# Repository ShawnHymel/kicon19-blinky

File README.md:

Blinky Pin for KiCon 2019
=========================

Pin badge developed for KiCon 2019. Workshop used to teach people the basics of KiCad.

Getting Started
---------------

Follow the instructions found in the [Worksheet - Intro to KiCad PDF](https://github.com/ShawnHymel/kicon19-blinky/blob/master/Documentation/Worksheet%20-%20Intro%20to%20KiCad.pdf).

Bill of Materials (BOM)
-----------------------

To build the pin/badge, refer to the [BOM file found here](https://github.com/ShawnHymel/kicon19-blinky/blob/master/Hardware/kicon19-blinky-bom.csv).

License
-------

The code is beerware; if you see me at the local, and you've found the code helpful, please buy me a round!

Board schematic and layout design found in the [Hardware directory](https://github.com/ShawnHymel/kicon19-blinky/tree/master/Hardware) are [CC BY 4.0](https://creativecommons.org/licenses/by/4.0/).

[Worksheet](https://github.com/ShawnHymel/kicon19-blinky/blob/master/Documentation/Worksheet%20-%20Intro%20to%20KiCad.pdf) is [CC BY 4.0](https://creativecommons.org/licenses/by/4.0/).

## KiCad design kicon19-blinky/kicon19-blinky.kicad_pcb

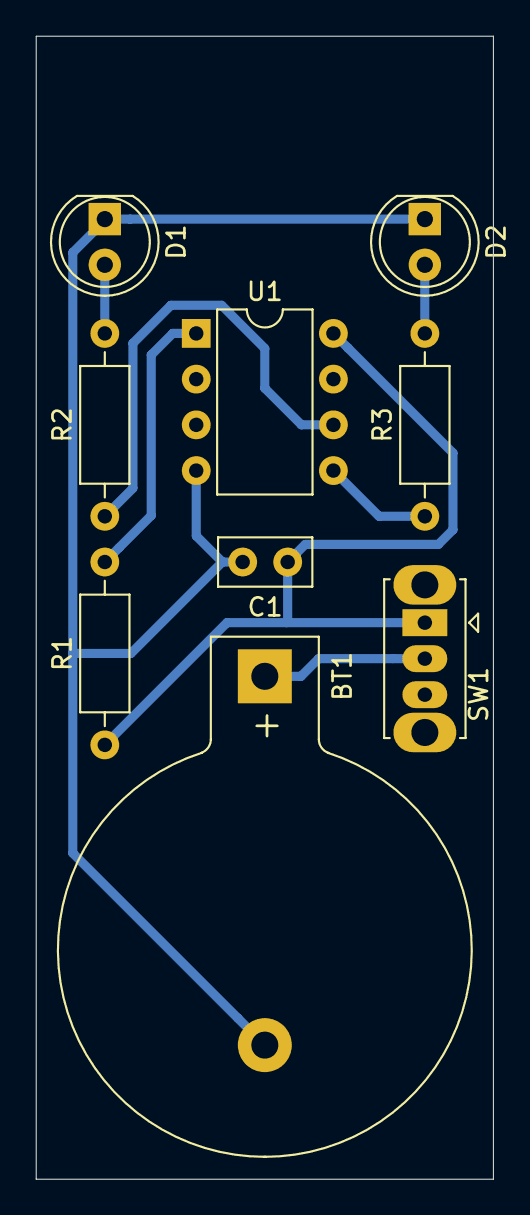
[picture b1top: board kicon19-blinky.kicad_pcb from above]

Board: 2 copper layers, 25.4 x 63.5 mm, 9 parts (0 on the bottom side), 8 nets.

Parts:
BT1: Battery_Cell; BatteryHolder_Keystone_103_1x20mm
C1: 10uF; C_Disc_D5.0mm_W2.5mm_P2.50mm
D1, D2: LED; LED_D5.0mm
R1: 10k; R_Axial_DIN0207_L6.3mm_D2.5mm_P10.16mm_Horizontal
R2, R3: 100; R_Axial_DIN0207_L6.3mm_D2.5mm_P10.16mm_Horizontal
SW1: SW_SPDT; SW_Slide_1P2T_CK_OS102011MS2Q
U1: ATtiny85-20PU; DIP-8_W7.62mm

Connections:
unnamed: BT1.1, SW1.2
unnamed: BT1.2, C1.2, D1.1, D2.1, U1.4
unnamed: C1.1, R1.1, SW1.1, U1.8
unnamed: D1.2, R2.2
unnamed: D2.2, R3.2
unnamed: R1.2, U1.1
unnamed: R2.1, U1.6
unnamed: R3.1, U1.5

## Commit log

2019-04-05 Initial schematic and part placement
2019-04-07 Finished board, added Arduino program
2019-04-07 Updated Arduino code for more linear blink
2019-04-22 Reorganized folders
2019-04-25 Updated sketch for low power. Added worksheet.
2019-04-26 Added THT lib
2019-04-26 Renamed lib
2019-04-26 Added battery lib
2019-05-01 Updated worksheet and added README
2019-05-01 Added license info to worksheet
